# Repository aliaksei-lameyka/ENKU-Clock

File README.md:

# ENKU Clock

Open, repairable, local-first e-paper alarm clock.

ENKU Clock is a compact ambient clock built around an e-paper display, physical controls and a warm wake-light. It is designed to work without subscriptions, advertisements or a mandatory cloud service.

## Status

**Rev A hardware — PCBWay DFM / prototype review**

The Rev A electronics set contains four PCBs:

| Board | Size | Layers | Status |
|---|---:|---:|---|
| Mainboard | 88 × 48 mm | 4 | Rev A validated, prototype package submitted |
| Encoder board | 24 × 23 mm | 2 | Rev A validated |
| Snooze board | 26 × 18 mm | 2 | Rev A validated |
| Wake LED board | 78 × 8 mm | 2 | Rev A validated |

The current revision has passed native KiCad manufacturing checks with zero hard DRC violations and zero unconnected items before prototype submission.

## Rev A hardware

## Design goals

- local-first operation
- no subscription or mandatory cloud account
- e-paper primary display
- physical rotary control and Snooze button
- warm wake-light
- repairable distributed-board construction
- documented connectors and service access
- replaceable external modules where practical
- open hardware and firmware development

## System overview

```mermaid
flowchart LR
    USB[USB-C] --> MAIN[Mainboard<br/>ESP32-S3 + power + RTC + audio + E Ink]
    BAT[1S LiPo<br/>BAT + NTC] --> MAIN
    EINK[E Ink display] <-->|24-pin FPC| MAIN
    FL[Frontlight] <-->|6-pin FPC| MAIN
    ENC[Encoder board] <-->|5-wire harness| MAIN
    SNZ[Snooze board] <-->|3-wire harness| MAIN
    LED[Wake LED board] <-->|2-wire harness| MAIN
    SPK[Speaker] <-->|2-wire harness| MAIN
```

The distributed layout keeps user controls and lighting mechanically independent from the Mainboard, improving serviceability and enclosure freedom.

## Hardware

The system is split into four boards:

- **Mainboard** — ESP32-S3, USB-C, battery charging and power path, RTC, ambient-light sensor, audio, e-paper interface and lighting control.
- **Encoder board** — side rotary control.
- **Snooze board** — top physical Snooze control.
- **Wake LED board** — independent warm-light LED board.

### Mainboard highlights

- ESP32-S3-WROOM-1
- USB-C
- BQ24074 charger / dynamic power path
- TPS62840 3.3 V regulator
- RV-3028-C7 RTC
- VEML7700 ambient-light sensor
- MAX98357A I2S amplifier
- external E Ink booster/interface
- service connectors for distributed controls and lighting

## Repository layout

```text
hardware/
  mainboard/          Mainboard KiCad PCB and manufacturing data
  daughterboards/     Encoder, Snooze and Wake LED boards
  schematics/         Rev A schematic sources
  libraries/          Project KiCad symbols and footprints
  assembly/           BOM data
docs/
  README.md
  architecture.md
  connectors.md
  mechanical-interface.md
  manufacturing.md
  bringup.md
  release-checklist.md
  repairability.md
  status.md
.github/
  ISSUE_TEMPLATE/
  workflows/
```

## Manufacturing

Rev A is currently under PCBWay prototype DFM / sourcing review. Production files are generated from the checked KiCad sources rather than maintained as hand-edited manufacturing files.

For the Mainboard, the baseline fabrication target is:

- 4-layer FR-4
- 1.6 mm
- 1 oz outer / inner copper
- ENIG
- L2 continuous GND reference
- L3 power / utility distribution
- filled/capped via-in-pad where explicitly required for SMT assembly

See [docs/manufacturing.md](docs/manufacturing.md).

## Documentation

- [Documentation index](docs/README.md)
- [Architecture](docs/architecture.md)
- [Connectors and GPIO](docs/connectors.md)
- [Mechanical interface](docs/mechanical-interface.md)
- [External components & harness BOM](docs/external-components.md)
- [Rev A procurement plan — 5 prototypes](docs/procurement-reva.md)
- [Manufacturing](docs/manufacturing.md)
- [Rev A bring-up checklist](docs/bringup.md)
- [Release checklist](docs/release-checklist.md)
- [Repairability](docs/repairability.md)
- [Project status](docs/status.md)

## Repairability

ENKU Clock uses separate boards for controls and lighting so service parts can be replaced independently. Connectors, polarity and functional interfaces are documented wherever practical.

See [docs/repairability.md](docs/repairability.md).

## Firmware

Firmware will live in this repository as the Rev A bring-up stabilizes. The first firmware milestone is a hardware bring-up image covering power, USB, RTC, ambient-light sensing, controls, audio, E Ink and lighting.

## Project stage

This is prototype hardware. Files may still change after DFM review and physical Rev A validation.

## License

The project is intended to be open source. Final hardware/firmware license files will be added before the first tagged public release.

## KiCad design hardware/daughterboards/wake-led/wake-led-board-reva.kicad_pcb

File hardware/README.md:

# Hardware

This directory contains the canonical ENKU Clock Rev A hardware source.

- `mainboard/` — 4-layer Mainboard PCB
- `daughterboards/` — Encoder, Snooze and Wake LED PCBs
- `schematics/` — hierarchical Rev A schematic sheets
- `libraries/` — project-specific KiCad libraries
- `assembly/` — assembly BOM data
- `footprint-plan.csv` — footprint planning reference

Generated Gerbers and production archives are release artifacts, not hand-maintained source files.

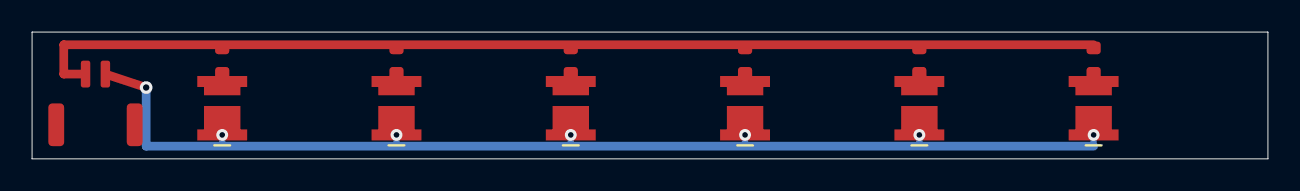
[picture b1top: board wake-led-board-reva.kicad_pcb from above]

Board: 2 copper layers, 78.0 x 8.0 mm, 13 parts (0 on the bottom side), 8 nets.

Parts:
D1, D2, D3, D4, D5, D6: NFSW757G-V3 2700K; Nichia_NFSW757G_V3
J1: SM02B-GHS-TB; JST_GH_SM02B-GHS-TB_1x02-1MP_P1.25mm_Horizontal
R1, R2, R3, R4, R5, R6: 56R; R_0603_1608Metric

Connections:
+3V3: J1.1, R1.2, R2.2, R3.2, R4.2, R5.2, R6.2
LED1_A: D1.2, R1.1
LED2_A: D2.2, R2.1
LED3_A: D3.2, R3.1
LED4_A: D4.2, R4.1
LED5_A: D5.2, R5.1
LED6_A: D6.2, R6.1
WAKE_LED_RETURN: D1.1, D2.1, D3.1, D4.1, D5.1, D6.1, J1.2

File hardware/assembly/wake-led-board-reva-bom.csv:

Designator,Qty,Manufacturer,MPN,Description,Footprint,Populate
J1,1,JST,SM02B-GHS-TB(LF)(SN),GH 1.25mm 2-pin right-angle SMD,JST_GH_SM02B-GHS-TB_1x02-1MP_P1.25mm_Horizontal,YES
D1 D2 D3 D4 D5 D6,6,Nichia,NFSW757G-V3,3030 warm-white LED 2700K; pad 1 = K/cathode = WAKE_LED_RETURN; exact Nichia 2700K CCT/CRI/order rank must be declared and approved before substitution,Nichia_NFSW757G_V3,YES
R1 R2 R3 R4 R5 R6,6,Generic,56R 1% 0603,56 ohm current-setting resistor 0603,R_0603_1608Metric,YES

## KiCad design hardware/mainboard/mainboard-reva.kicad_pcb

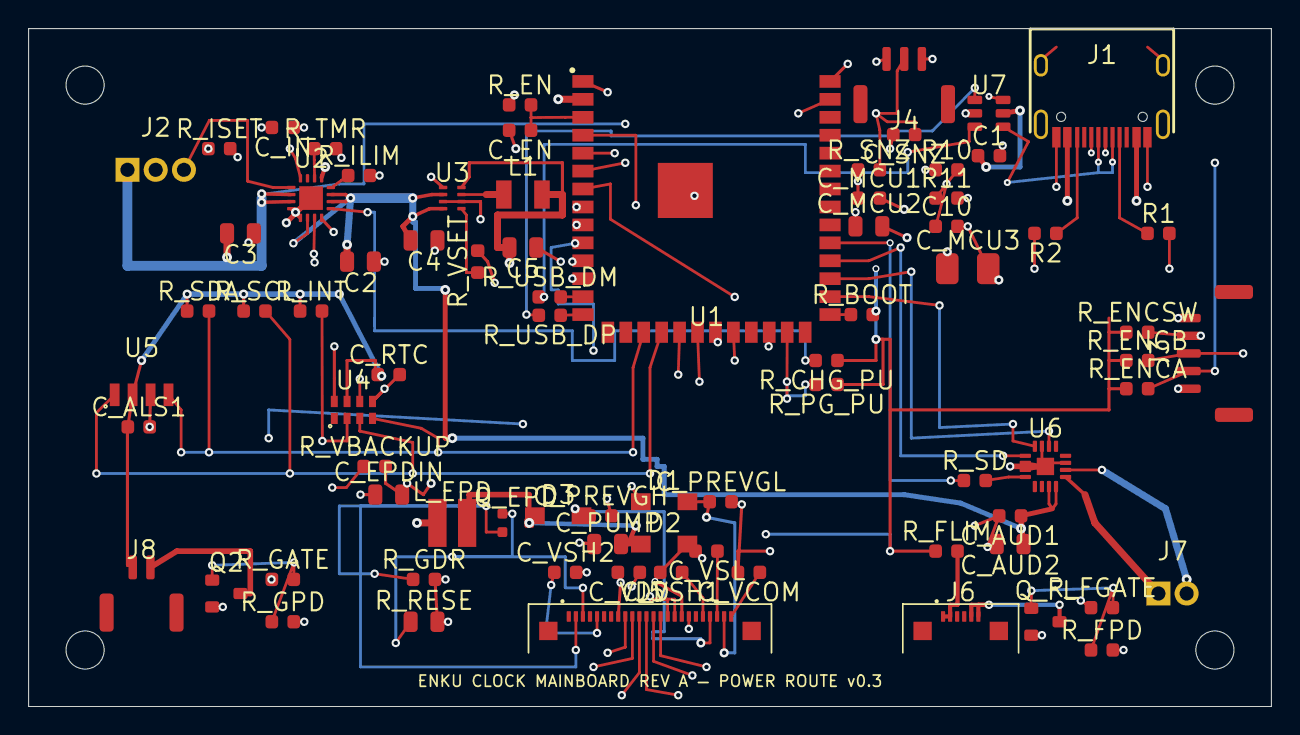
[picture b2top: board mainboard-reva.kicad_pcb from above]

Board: 4 copper layers, 88.0 x 48.0 mm, 82 parts (0 on the bottom side), 63 nets.

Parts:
C1: 1uF/10V; C_0603_1608Metric
C2: 4.7uF SYS; C_0805_2012Metric
C3: 4.7uF BAT; C_0805_2012Metric
C4: 4.7uF; C_0805_2012Metric
C5: 10uF; C_0805_2012Metric
C10: 100nF; C_0603_1608Metric
C_ALS1: 100nF; C_0603_1608Metric
C_AUD1: 100nF; C_0603_1608Metric
C_AUD2: 10uF; C_0805_2012Metric
C_EN: 1uF; C_0603_1608Metric
C_EPDIN: 4.7uF/50V; C_0805_2012Metric
C_IN: 1uF/10V; C_0603_1608Metric
C_MCU1: 100nF; C_0603_1608Metric
C_MCU2: 10uF; C_0805_2012Metric
C_MCU3: 100uF low-ESR; C_1210_3225Metric
C_PREVGH: 1uF/50V; C_0603_1608Metric
C_PREVGL: 1uF/50V; C_0603_1608Metric
C_PUMP: 4.7uF/50V; C_0805_2012Metric
C_RTC: 100nF; C_0603_1608Metric
C_SNZ: 10nF; C_0603_1608Metric
C_VCOM: 1uF/50V; C_0603_1608Metric
C_VDD: 1uF/50V; C_0603_1608Metric
C_VSH1, C_VSH2: 1uF/50V; C_0603_1608Metric
C_VSL: 1uF/50V; C_0603_1608Metric
D1, D2, D3: MBR0530; D_SOD-123
H1, H2, H3, H4: MountingHole_2.7mm_M2.5
J1: USB-C; HRO-TYPE-C-31-M-12
J2: BATTERY; JST_PH_S3B-PH-K_1x03_P2.00mm_Horizontal
J3: SM05B-GHS-TB / ENCODER; JST_GH_SM05B-GHS-TB_1x05-1MP_P1.25mm_Horizontal
J4: SM03B-GHS-TB / SNOOZE; JST_GH_SM03B-GHS-TB_1x03-1MP_P1.25mm_Horizontal
J5: Molex 54550-2472 / GDEY037T03-FL21; Molex_54550_24P_0.5mm
J6: Molex 54550-0672 / FL21 frontlight; Molex_54550_6P_0.5mm
J7: SPEAKER; JST_PH_S2B-PH-K_1x02_P2.00mm_Horizontal
J8: SM02B-GHS-TB / WAKE_LED; JST_GH_SM02B-GHS-TB_1x02-1MP_P1.25mm_Horizontal
L1: 2.2uH; L_3.2x2.5mm_H1.2mm
L_EPD: 74438335100 10uH; WE-MAPI_3015_74438335100
Q2: AO3400A / WAKE; SOT-23
Q_EPD: SI1308EDL-T1-GE3; SOT-323_SC-70
Q_FL: AO3400A / FRONTLIGHT; SOT-23
R1: 5.1k CC1; R_0603_1608Metric
R2: 5.1k CC2; R_0603_1608Metric
R10: 1M 1%; R_0603_1608Metric
R11: 330k 1%; R_0603_1608Metric
R_BOOT: 10k; R_0603_1608Metric
R_CHG_PU: 10k; R_0603_1608Metric
R_EN: 10k; R_0603_1608Metric
R_ENCA: 10k; R_0603_1608Metric
R_ENCB: 10k; R_0603_1608Metric
R_ENCSW: 10k; R_0603_1608Metric
R_FGATE: 47R; R_0603_1608Metric
R_FLIM: 10R / tune; R_0603_1608Metric
R_FPD: 100k; R_0603_1608Metric
R_GATE: 47R; R_0603_1608Metric
R_GDR: 10k 1%; R_0603_1608Metric
R_GPD: 100k; R_0603_1608Metric
R_ILIM: 1.18k; R_0603_1608Metric
R_INT: 10k; R_0603_1608Metric
R_ISET: 1.13k; R_0603_1608Metric
R_PG_PU: 10k; R_0603_1608Metric
R_RESE: 0.47R 1%; R_0805_2012Metric
R_SCL: 4.7k; R_0603_1608Metric
R_SD: 2.2k; R_0603_1608Metric
R_SDA: 4.7k; R_0603_1608Metric
R_SNZ: 10k; R_0603_1608Metric
R_TMR: 68k; R_0603_1608Metric
R_USB_DM: 22R; R_0603_1608Metric
R_USB_DP: 22R; R_0603_1608Metric
R_VBACKUP: 10k; R_0603_1608Metric
R_VSET: 267k 1%; R_0603_1608Metric
U1: ESP32-S3-WROOM-1-N8; ESP32-S3-WROOM-1_ENKU
U2: BQ24074RGTR; BQ24074_RGT
U3: TPS62840DLCR; TPS62840_DLC0008B
U4: RV-3028-C7
U5: VEML7700
U6: MAX98357AETE+T; MAX98357A_ETE_TQFN16
U7: USBLC6-2SC6; SOT-23-6

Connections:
+3V3: C5.1, C_ALS1.1, C_EPDIN.1, C_MCU1.1, C_MCU2.1, C_MCU3.1, C_RTC.1, J5.15, J5.16, J8.1, L1.2, L_EPD.1, R_BOOT.2, R_CHG_PU.1, R_EN.1, R_ENCA.1, R_ENCB.1, R_ENCSW.1, R_FLIM.1, R_INT.1, R_PG_PU.1, R_SCL.1, R_SDA.1, R_SNZ.1, U1.2, U3.8, U4.7, U5.2
AMP_SD: R_SD.2, U6.4
AMP_SD_MCU: R_SD.1, U1.31
BAT+: C3.1, J2.1, R10.1, U2.2, U2.3
BAT_ADC: C10.1, R10.2, R11.1, U1.39
BAT_NTC: J2.3, U2.1
BOOT0: R_BOOT.1, U1.27
BUCK_VSET: R_VSET.1, U3.5
CHG_ILIM: R_ILIM.1, U2.12
CHG_ISET: R_ISET.1, U2.16
CHG_STATUS: R_CHG_PU.2, U1.24, U2.9
CHG_TMR: R_TMR.1, U2.14
EN: C_EN.1, R_EN.2, U1.3
ENC_A: J3.2, R_ENCA.2, U1.6
ENC_B: J3.3, R_ENCB.2, U1.7
ENC_SW: J3.4, R_ENCSW.2, U1.12
EPD_BUSY: J5.9, U1.9
EPD_CS: J5.12, U1.21
EPD_DC: J5.11, U1.22
EPD_GDR: J5.2, Q_EPD.2, R_GDR.1
EPD_MOSI: J5.14, U1.20
EPD_PUMP: C_PUMP.1, D1.1
EPD_RESE: J5.3, Q_EPD.1, R_RESE.1
EPD_RST: J5.10, U1.8
EPD_SCK: J5.13, U1.19
EPD_SW: C_PUMP.2, D2.1, D3.1, L_EPD.2, Q_EPD.3
EPD_VCOM: C_VCOM.1, J5.24
EPD_VDD: C_VDD.1, J5.18
EPD_VSH1: C_VSH1.1, J5.20
EPD_VSH2: C_VSH2.1, J5.5
EPD_VSL: C_VSL.1, J5.22
FL_GATE: Q_FL.1, R_FGATE.2, R_FPD.1
FL_LED+: J6.1, J6.2, R_FLIM.2
FL_LED_RETURN: J6.5, J6.6, Q_FL.3
FRONTLIGHT_PWM: R_FGATE.1, U1.11
GND: C1.2, C2.2, C3.2, C4.2, C5.2, C10.2, C_ALS1.2, C_AUD1.2, C_AUD2.2, C_EN.2, C_EPDIN.2, C_IN.2, C_MCU1.2, C_MCU2.2, C_MCU3.2, C_PREVGH.2, C_PREVGL.2, C_RTC.2, C_SNZ.2, C_VCOM.2, C_VDD.2, C_VSH1.2, C_VSH2.2, C_VSL.2, D2.2, J1.A1, J1.A12, J1.S1, J2.2, J3.1, J3.5, J4.1, J4.3, J5.8, J5.17, Q2.2, Q_FL.2, R1.2, R2.2, R11.2, R_FPD.2, R_GDR.2, R_GPD.2, R_ILIM.2, R_ISET.2, R_RESE.2, R_TMR.2, R_VBACKUP.2, R_VSET.2, U1.1, U1.40, U1.41, U2.4, U2.5, U2.8, U2.17, U3.1, U3.3, U3.6, U4.5, U4.8, U5.3, U6.2, U6.3, U6.11, U6.15, U6.17, U7.2
I2C_SCL: R_SCL.2, U1.18, U4.3, U5.1
I2C_SDA: R_SDA.2, U1.17, U4.4, U5.4
I2S_BCLK: U1.28, U6.16
I2S_DOUT: U1.30, U6.1
I2S_LRCLK: U1.29, U6.14
POWER_GOOD: R_PG_PU.2, U1.25, U2.7
PREVGH: C_PREVGH.1, D3.2, J5.21
PREVGL: C_PREVGL.1, D1.2, J5.23
RTC_INT: R_INT.2, U1.4, U4.2
RTC_VBACKUP: R_VBACKUP.1, U4.6
SNOOZE_SW: C_SNZ.1, J4.2, R_SNZ.2, U1.5
SPK+: J7.1, U6.9
SPK-: J7.2, U6.10
SW_3V3: L1.1, U3.7
SYS_RAW: C2.1, C4.1, C_AUD1.1, C_AUD2.1, U2.6, U2.10, U2.11, U3.2, U3.4, U6.7, U6.8
USB_CC1: J1.A5, R1.1
USB_CC2: J1.B5, R2.1
USB_D+: R_USB_DP.1, U7.1
USB_D+_CONN: J1.A6, J1.B6, U7.6
USB_D+_MCU: R_USB_DP.2, U1.14
USB_D-: R_USB_DM.1, U7.3
USB_D-_CONN: J1.A7, J1.B7, U7.4
USB_D-_MCU: R_USB_DM.2, U1.13
VBUS_USB: C1.1, C_IN.1, J1.A4, J1.A9, U2.13, U7.5
WAKE_GATE: Q2.1, R_GATE.2, R_GPD.1
WAKE_LED_PWM: R_GATE.1, U1.10
WAKE_LED_RETURN: J8.2, Q2.3

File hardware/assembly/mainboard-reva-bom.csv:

Designator,Quantity,Value,Footprint,Assembly note
"C_ALS1,C_AUD1,C_MCU1,C_RTC,C10",5,"100nF","Capacitor_SMD:C_0603_1608Metric",""
"C_AUD2,C_MCU2,C5",3,"10uF","Capacitor_SMD:C_0805_2012Metric",""
"C_EN",1,"1uF","Capacitor_SMD:C_0603_1608Metric",""
"C_SNZ",1,"10nF","Capacitor_SMD:C_0603_1608Metric","Snooze hardware debounce / EMI filter; populated in Rev A"
"C_IN",1,"1uF/10V","Capacitor_SMD:C_0603_1608Metric","Local BQ24074 IN bypass; place close to U2 IN/GND"
"C_EPDIN,C_PUMP",2,"4.7uF/50V","Capacitor_SMD:C_0805_2012Metric","GDEY037T03-FL21 reference requires X5R/X7R and >=25V; proposed Samsung CL21A475KBQNNNE is 4.7uF 50V X5R"
"C_MCU3",1,"100uF low-ESR","Capacitor_SMD:C_1210_3225Metric",""
"C_PREVGH,C_PREVGL,C_VCOM,C_VDD,C_VSH1,C_VSH2,C_VSL",7,"1uF/50V","Capacitor_SMD:C_0603_1608Metric","GDEY037T03-FL21 reference requires X5R/X7R and >=25V; proposed Samsung CL10B105KB8NQNC is 1uF 50V X7R"
"C1",1,"1uF/10V","Capacitor_SMD:C_0603_1608Metric",""
"C2",1,"4.7uF SYS","Capacitor_SMD:C_0805_2012Metric",""
"C3",1,"4.7uF BAT","Capacitor_SMD:C_0805_2012Metric",""
"C4",1,"4.7uF","Capacitor_SMD:C_0805_2012Metric",""
"D1,D2,D3",3,"MBR0530","Diode_SMD:D_SOD-123",""
"J1",1,"USB-C","ENKU_Clock:HRO-TYPE-C-31-M-12","HRO TYPE-C-31-M-12 or footprint-compatible approved equivalent"
"J2",1,"BATTERY","Connector_JST:JST_PH_S3B-PH-K_1x03_P2.00mm_Horizontal","3-wire 1S Li-ion/LiPo pack required; TEMP must be 10k NTC to PACK-/GND"
"J3",1,"SM05B-GHS-TB / ENCODER","Connector_JST:JST_GH_SM05B-GHS-TB_1x05-1MP_P1.25mm_Horizontal",""
"J4",1,"SM03B-GHS-TB / SNOOZE","Connector_JST:JST_GH_SM03B-GHS-TB_1x03-1MP_P1.25mm_Horizontal",""
"J5",1,"Molex 54550-2472 / GDEY037T03-FL21","ENKU_Clock:Molex_54550_24P_0.5mm","Molex 54550-2472, 24-pin 0.5mm FPC"
"J6",1,"Molex 54550-0672 / FL21 frontlight","ENKU_Clock:Molex_54550_6P_0.5mm","Molex 54550-0672, 6-pin 0.5mm FPC; FL21 pins 1-2 LED+, 3-4 NC, 5-6 LED-"
"J7",1,"SPEAKER","Connector_JST:JST_PH_S2B-PH-K_1x02_P2.00mm_Horizontal",""
"J8",1,"SM02B-GHS-TB / WAKE_LED","Connector_JST:JST_GH_SM02B-GHS-TB_1x02-1MP_P1.25mm_Horizontal",""
"L_EPD",1,"74438335100 10uH","ENKU_Clock:WE-MAPI_3015_74438335100","Locked prototype MPN: Wurth 74438335100; 3.0x3.0x1.5mm, 1.25A rated, 2A Isat; land pattern matched to manufacturer recommendation"
"L1",1,"2.2uH","Inductor_SMD:L_3.2x2.5mm_H1.2mm","Preferred prototype MPN: Delta/Cyntec VCTA32251B-2R2MS6"
"Q_EPD",1,"SI1308EDL-T1-GE3","Package_TO_SOT_SMD:SOT-323_SC-70",""
"Q_FL",1,"AO3400A / FRONTLIGHT","Package_TO_SOT_SMD:SOT-23",""
"Q2",1,"AO3400A / WAKE","Package_TO_SOT_SMD:SOT-23",""
"R_BOOT,R_CHG_PU,R_EN,R_ENCA,R_ENCB,R_ENCSW,R_INT,R_PG_PU,R_SNZ,R_VBACKUP",10,"10k","Resistor_SMD:R_0603_1608Metric","R_ENCA/R_ENCB/R_ENCSW/R_SNZ are external pull-ups for remote mechanical controls"
"R_SCL,R_SDA",2,"4.7k","Resistor_SMD:R_0603_1608Metric","I2C pull-ups; aligned with VEML7700 application guidance"
"R_FGATE,R_GATE",2,"47R","Resistor_SMD:R_0603_1608Metric",""
"R_FLIM",1,"10R / tune","Resistor_SMD:R_0603_1608Metric","Rev A optical/current-limit starting value; confirm 10R before assembly"
"R_FPD,R_GPD",2,"100k","Resistor_SMD:R_0603_1608Metric",""
"R_GDR",1,"10k 1%","Resistor_SMD:R_0603_1608Metric","EPD GDR gate pull-down; reference booster value"
"R10",1,"1M 1%","Resistor_SMD:R_0603_1608Metric","Battery ADC upper divider resistor"
"R_ILIM",1,"1.18k","Resistor_SMD:R_0603_1608Metric","BQ24074 input current-limit programming resistor"
"R_ISET",1,"1.13k","Resistor_SMD:R_0603_1608Metric",""
"R_RESE",1,"0.47R 1%","Resistor_SMD:R_0805_2012Metric",""
"R_SD",1,"2.2k","Resistor_SMD:R_0603_1608Metric",""
"R_TMR",1,"68k","Resistor_SMD:R_0603_1608Metric","BQ24074 safety timer ~9.1h typical; margin for ~3Ah battery in USB500 mode"
"R_USB_DM,R_USB_DP",2,"22R","Resistor_SMD:R_0603_1608Metric",""
"R_VSET",1,"267k 1%","Resistor_SMD:R_0603_1608Metric",""
"R1",1,"5.1k CC1","Resistor_SMD:R_0603_1608Metric",""
"R2",1,"5.1k CC2","Resistor_SMD:R_0603_1608Metric",""
"R11",1,"330k 1%","Resistor_SMD:R_0603_1608Metric",""
"U1",1,"ESP32-S3-WROOM-1-N8","ENKU_Clock:ESP32-S3-WROOM-1_ENKU",""
"U2",1,"BQ24074RGTR","ENKU_Clock:BQ24074_RGT",""
"U3",1,"TPS62840DLCR","ENKU_Clock:TPS62840_DLC0008B",""
"U4",1,"RV-3028-C7 TA QC","ENKU_Clock:RV-3028-C7","Micro Crystal commercial grade, -40 to +85C"
"U5",1,"VEML7700","ENKU_Clock:VEML7700",""
"U6",1,"MAX98357AETE+T","ENKU_Clock:MAX98357A_ETE_TQFN16","EP tied to GND copper and adjacent through-via outside thermal pad; no via-in-pad process required"
"U7",1,"USBLC6-2SC6","Package_TO_SOT_SMD:SOT-23-6",""

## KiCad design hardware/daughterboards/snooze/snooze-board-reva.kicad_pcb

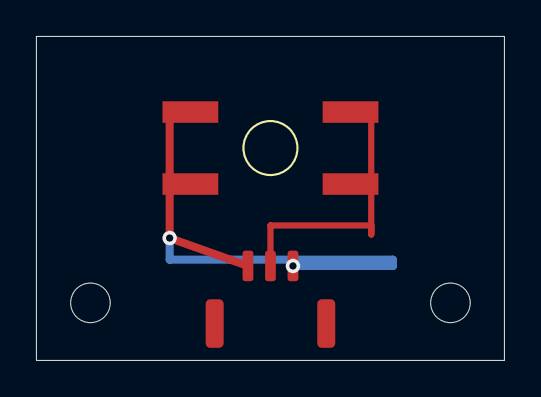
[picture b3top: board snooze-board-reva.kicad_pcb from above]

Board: 2 copper layers, 26.0 x 18.0 mm, 4 parts (0 on the bottom side), 2 nets.

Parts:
H1, H2: MountingHole_2.2mm_M2
J1: SM03B-GHS-TB; JST_GH_SM03B-GHS-TB_1x03-1MP_P1.25mm_Horizontal
SW1: KSC221GLFS

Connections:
GND: J1.1, J1.3, SW1.1
SNOOZE_SW: J1.2, SW1.2

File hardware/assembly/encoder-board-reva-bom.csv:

Designator,Qty,Manufacturer,MPN,Description,Footprint,Populate
J1,1,JST,SM05B-GHS-TB(LF)(SN),GH 1.25mm 5-pin right-angle SMD,JST_GH_SM05B-GHS-TB_1x05-1MP_P1.25mm_Horizontal,YES
SW1,1,ALPS Alpine,EC11E15244G1,11mm rotary encoder 30 detents/15 pulses with push switch,RotaryEncoder_Alps_EC11E-Switch_Vertical_H20mm,YES
H1 H2,2,,,M2 mounting hole,2.2mm drill,NO

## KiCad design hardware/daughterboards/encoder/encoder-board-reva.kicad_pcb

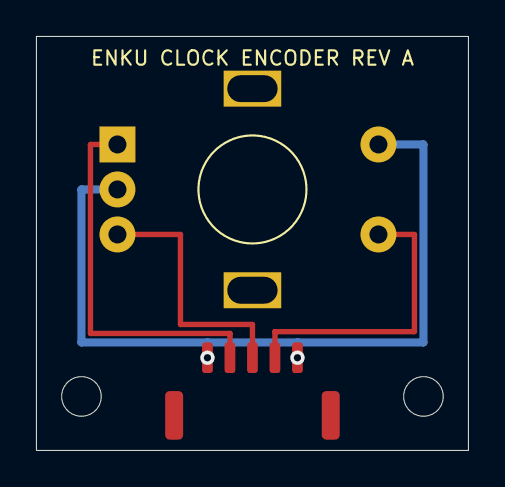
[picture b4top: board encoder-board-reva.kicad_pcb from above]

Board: 2 copper layers, 24.0 x 23.0 mm, 4 parts (0 on the bottom side), 4 nets.

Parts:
H1, H2: MountingHole_2.2mm_M2
J1: SM05B-GHS-TB; JST_GH_SM05B-GHS-TB_1x05-1MP_P1.25mm_Horizontal
SW1: EC11E15244G1; RotaryEncoder_Alps_EC11E-Switch_Vertical_H20mm

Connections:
ENC_A: J1.2, SW1.A
ENC_B: J1.3, SW1.B
ENC_SW: J1.4, SW1.S1
GND: J1.1, J1.5, SW1.C, SW1.S2

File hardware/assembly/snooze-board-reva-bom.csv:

Designator,Qty,Manufacturer,MPN,Description,Footprint,Populate
J1,1,JST,SM03B-GHS-TB(LF)(SN),GH 1.25mm 3-pin right-angle SMD,JST_GH_SM03B-GHS-TB_1x03-1MP_P1.25mm_Horizontal,YES
SW1,1,C&K,KSC221GLFS,Sealed tactile switch SPST 2N 6.2x6.2mm,KSC221GLFS,YES
H1 H2,2,,,M2 mounting hole,2.2mm drill,NO
